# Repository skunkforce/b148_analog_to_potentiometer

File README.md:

# edgy_board number b148
This design is part of the [edgy board project](https://github.com/skunkforce/edgy_boards). 

# getting started
This repository uses submodules. After cloning use the command 

```$ git submodule update --init --recursive```

to pull the submodules before opening the project with kicad. 

# Tests
Tests can be found in [TESTS.md](TESTS.md)

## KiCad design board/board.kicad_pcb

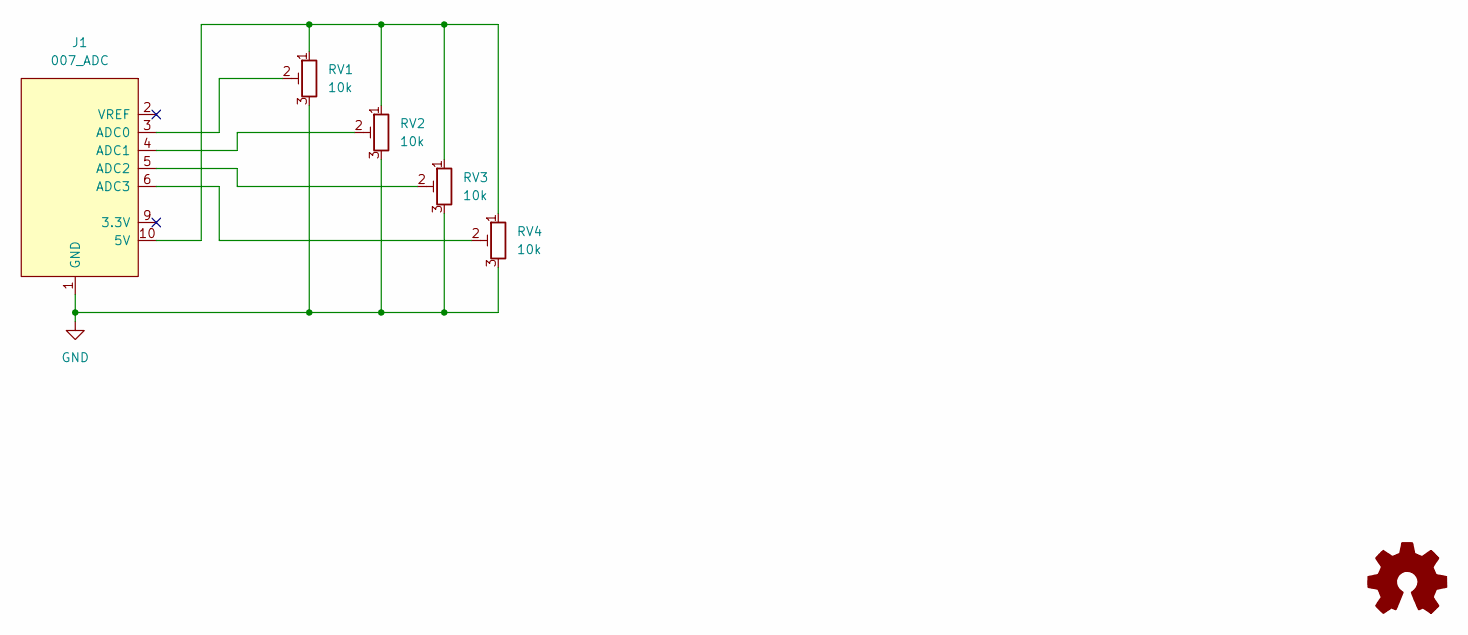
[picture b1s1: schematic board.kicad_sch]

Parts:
J1: 007_ADC; on_edge_2x05_device
LOGO1: Logo_Open_Hardware_Small; OSHW-Symbol_6.7x6mm_SilkScreen
RV1, RV2, RV3, RV4: 10k; Potentiometer_Bourns_TC33X_Vertical; lcsc C719176

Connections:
GND: J1.1 (GND), RV1.3, RV2.3, RV3.3, RV4.3
unnamed: J1.10 (5V), RV1.1, RV2.1, RV3.1, RV4.1
unnamed: J1.3 (ADC0), RV1.2
unnamed: J1.4 (ADC1), RV2.2
unnamed: J1.5 (ADC2), RV3.2
unnamed: J1.6 (ADC3), RV4.2

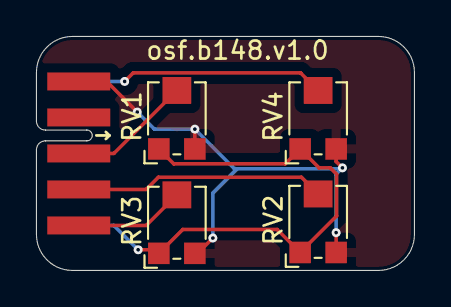
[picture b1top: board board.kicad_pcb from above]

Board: 2 copper layers, 21.0 x 13.0 mm, 6 parts (1 on the bottom side), 6 nets.

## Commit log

2024-01-04 initial
2024-01-14 initial b148
